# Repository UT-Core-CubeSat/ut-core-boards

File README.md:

# UT-CORE-BOARDS

PCB designs and board requirements for UT-CORE.

## Structure

Each subsystem contains its boards. Each board has the same three folders:

```text
<subsystem>/<board>/
├── hardware/       # Existing KiCad projects and their supporting files
├── docs/           # Board requirements and existing documentation
└── datasheets/     # Component datasheets and manufacturer references
```

Keep KiCad projects, libraries, models, schematic sheets, and other project
dependencies together. Existing revision folders, backups, manufacturing
outputs, and simulations are preserved inside `hardware/`.

## Boards

| Subsystem | Board requirements | Hardware |
|-----------|--------------------|----------|
| ADCS | [Controller](ADCS/controller/docs/adcs-board-requirements.md) | [Projects](ADCS/controller/hardware/) |
| ADCS | [Motor](ADCS/motor/docs/motor-board-requirements.md) | [Projects](ADCS/motor/hardware/) |
| CDH | [Controller](CDH/controller/docs/cdh-board-requirements.md) | [Projects](CDH/controller/hardware/) |
| EPS | [Battery](EPS/battery/docs/battery-board-requirements.md) | [Projects](EPS/battery/hardware/) |
| EPS | [Solar panel](EPS/solar-panel/docs/solar-panel-board-requirements.md) | [Projects](EPS/solar-panel/hardware/) |
| EPS | [Solar conglomerator](EPS/solar-conglomerator/docs/solar-conglomerator-board-requirements.md) | [Projects](EPS/solar-conglomerator/hardware/) |
| EPS | [Magtest](EPS/magtest/docs/magtest-board-requirements.md) | [PCB](EPS/magtest/hardware/) |
| GNSS | [Receiver](GNSS/receiver/docs/gnss-board-requirements.md) | [Projects](GNSS/receiver/hardware/) |

Solar panel variants stay together under `EPS/solar-panel/hardware/`, with
their original project folders intact. Both battery project bundles are
preserved under `EPS/battery/hardware/`. The standalone `magtest.kicad_pcb`
is preserved separately; its purpose and status still are undocumented.

## Board documents

Use [the template](templates/name-board-requirements.md) and name each document
`<name>-board-requirements.md`, using lowercase words separated by hyphens.
Existing documents and sheets remain alongside them in `docs/` as references.

The five sections cover purpose and design, specifications, interfaces,
operation and limitations, and notes. Keep detailed implementation and design
history in the board files and PRs. Identify the applicable PCB revision and
mark unknown or unverified information clearly.

Existing project-local libraries and models have not been consolidated or
renamed. Any datasheets already embedded in a project should stay there if
moving them could affect references; the new `datasheets/` folders are for
standalone references.

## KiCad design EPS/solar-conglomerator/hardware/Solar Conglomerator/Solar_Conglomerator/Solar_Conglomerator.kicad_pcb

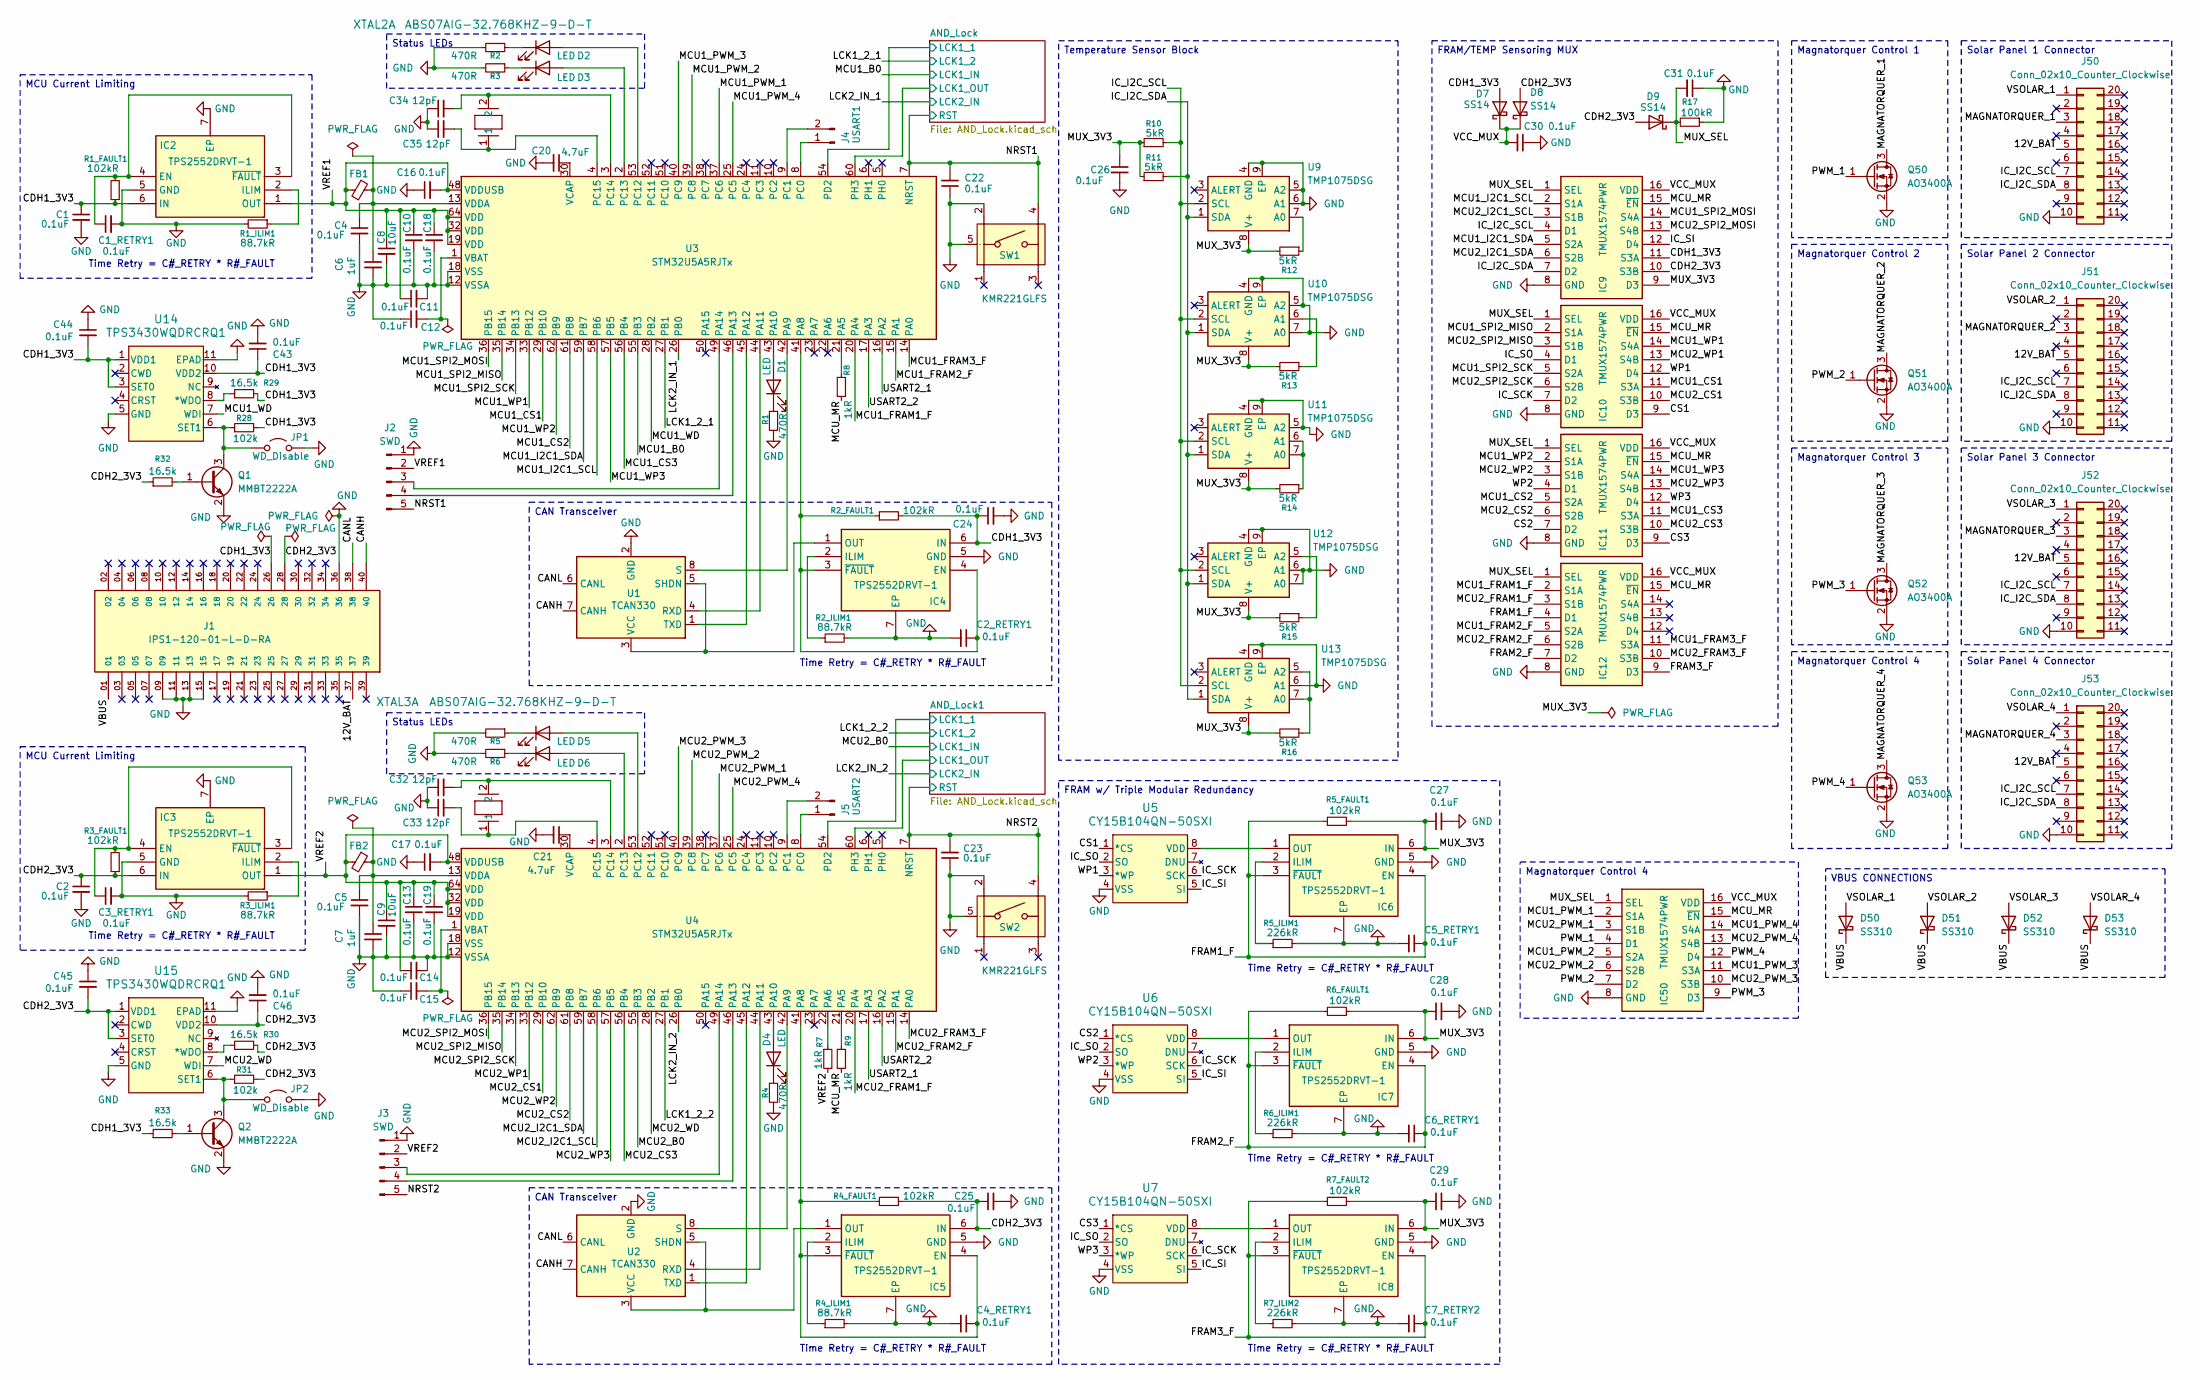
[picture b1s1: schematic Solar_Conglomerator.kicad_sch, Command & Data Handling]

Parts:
C1, C1_RETRY1, C2, C2_RETRY1, C3_RETRY1, C4, C4_RETRY1, C5, C5_RETRY1, C6_RETRY1, C7_RETRY2, C10, C11, C12, C13, C14, C15, C16, C17, C18, C19, C22, C23, C24, C25, C26, C27, C28, C29, C30, C31, C43, C44, C45, C46: 0.1uF; C_0603_1608Metric_Pad1.08x0.95mm_HandSolder
C6, C7: 1uF; C_0805_2012Metric_Pad1.18x1.45mm_HandSolder
C8, C9: 10uF; C_0805_2012Metric_Pad1.18x1.45mm_HandSolder
C20, C21: 4.7uF; C_0805_2012Metric_Pad1.18x1.45mm_HandSolder
C32, C33, C34, C35: 12pF; C_0603_1608Metric_Pad1.08x0.95mm_HandSolder
D1, D2, D3, D4, D5, D6: LED; LED_0201_0603Metric_Pad0.64x0.40mm_HandSolder
D7, D8, D9: SS14; D_SMA
D50, D51, D52, D53: SS310; D_SMA
FB1, FB2: FerriteBead_Small; R_0805_2012Metric_Pad1.20x1.40mm_HandSolder
IC2, IC3, IC4, IC5, IC6, IC7, IC8: TPS2552DRVT-1; Mouser Part Number 595-TPS2552DRVT-1
IC9, IC10, IC11, IC12, IC50: TMUX1574PWR; Mouser Part Number 595-TMUX1574PWR
J1: IPS1-120-01-L-D-RA
J2, J3: SWD; PinHeader_1x05_P2.54mm_Vertical
J4: USART1; PinHeader_1x02_P2.54mm_Vertical
J5: USART2; PinHeader_1x02_P2.54mm_Vertical
J50, J51, J52, J53: Conn_02x10_Counter_Clockwise; PinHeader_2x10_P2.54mm_Vertical
JP1, JP2: WD_Disable; TestPoint_2Pads_Pitch2.54mm_Drill0.8mm
Q1, Q2: MMBT2222A; SOT-23
Q50, Q51, Q52, Q53: AO3400A; SOT-23
R1, R2, R3, R4, R5, R6: 470R; R_0805_2012Metric_Pad1.20x1.40mm_HandSolder
R1_FAULT1, R2_FAULT1, R3_FAULT1, R4_FAULT1, R5_FAULT1, R6_FAULT1, R7_FAULT2: 102kR; R_0805_2012Metric_Pad1.20x1.40mm_HandSolder
R1_ILIM1, R2_ILIM1, R3_ILIM1, R4_ILIM1: 88.7kR; R_0805_2012Metric_Pad1.20x1.40mm_HandSolder
R5_ILIM1, R6_ILIM1, R7_ILIM2: 226kR; R_0805_2012Metric_Pad1.20x1.40mm_HandSolder
R7, R8, R9: 1kR; R_0805_2012Metric_Pad1.20x1.40mm_HandSolder
R10, R11, R12, R13, R14, R15, R16: 5kR; R_0603_1608Metric_Pad0.98x0.95mm_HandSolder
R17: 100kR; R_0805_2012Metric_Pad1.20x1.40mm_HandSolder
R28, R31: 102k; R_0805_2012Metric_Pad1.20x1.40mm_HandSolder
R29, R30, R32, R33: 16.5k; R_0805_2012Metric_Pad1.20x1.40mm_HandSolder
SW1, SW2: KMR221GLFS; Manufacturer Part KMR221GLFS; LCSC Part Name 4.6*2.8*1.9mm 立贴 轻触开关
U1, U2: TCAN330; SOIC-8_3.9x4.9mm_P1.27mm
U3, U4: STM32U5A5RJTx; LQFP-64_10x10mm_P0.5mm
U5, U6, U7: CY15B104QN-50SXI
U9, U10, U11, U12, U13: TMP1075DSG; WSON-8-1EP_2x2mm_P0.5mm_EP0.9x1.6mm
U14, U15: TPS3430WQDRCRQ1
XTAL2, XTAL3: ABS07AIG-32.768KHZ-9-D-T; XTAL_ABS07AIG_ABR

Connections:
/12V_BAT: J1.37, J50.5, J51.5, J52.5, J53.5
/AND_Lock1/LCK1_1: U4.54 (PD2); also elsewhere on the board
/AND_Lock1/LCK1_OUT: U4.60 (PH3); also elsewhere on the board
/AND_Lock/LCK1_1: U3.54 (PD2); also elsewhere on the board
/AND_Lock/LCK1_OUT: U3.60 (PH3); also elsewhere on the board
/CANH: J1.40, U1.7 (CANH), U2.7 (CANH)
/CANL: J1.38, U1.6 (CANL), U2.6 (CANL)
/CDH1_3V3: C1.1, C24.1, C43.1, C44.2, D7.2 (A), IC2.6 (IN), IC4.6 (IN), IC9.11 (S3A), J1.26, R1_FAULT1.1, R2_FAULT1.2, R28.2, R29.2, R33.1, U14.1 (VDD1), U14.3 (SET0), U14.10 (VDD2); also elsewhere on the board
/CDH2_3V3: C2.1, C25.1, C45.2, C46.1, D8.2 (A), D9.2 (A), IC3.6 (IN), IC5.6 (IN), IC9.10 (S3B), J1.28, R3_FAULT1.1, R4_FAULT1.2, R30.2, R31.2, R32.1, U15.1 (VDD1), U15.3 (SET0), U15.10 (VDD2); also elsewhere on the board
/CS1: IC10.9 (D3), U5.1 (*CS)
/CS2: IC11.7 (D2), U6.1 (*CS)
/CS3: IC11.9 (D3), U7.1 (*CS)
/FRAM1_F: C5_RETRY1.1, IC6.3 (~FAULT), IC6.4 (EN), IC12.4 (D1), R5_FAULT1.1
/FRAM2_F: C6_RETRY1.1, IC7.3 (~FAULT), IC7.4 (EN), IC12.7 (D2), R6_FAULT1.1
/FRAM3_F: C7_RETRY2.1, IC8.3 (~FAULT), IC8.4 (EN), IC12.9 (D3), R7_FAULT2.1
/IC_I2C_SCL: IC9.4 (D1), J50.7, J51.7, J52.7, J53.7, R10.2, U9.2 (SCL), U10.2 (SCL), U11.2 (SCL), U12.2 (SCL), U13.2 (SCL)
/IC_I2C_SDA: IC9.7 (D2), J50.8, J51.8, J52.8, J53.8, R11.2, U9.1 (SDA), U10.1 (SDA), U11.1 (SDA), U12.1 (SDA), U13.1 (SDA)
/IC_SCK: IC10.7 (D2), U5.6 (SCK), U6.6 (SCK), U7.6 (SCK)
/IC_SI: IC9.12 (D4), U5.5 (SI), U6.5 (SI), U7.5 (SI)
/IC_SO: IC10.4 (D1), U5.2 (SO), U6.2 (SO), U7.2 (SO)
/LCK1_2_1: U3.27 (PB1); also elsewhere on the board
/LCK1_2_2: U4.27 (PB1); also elsewhere on the board
/LCK2_IN_1: U3.26 (PB0); also elsewhere on the board
/LCK2_IN_2: U4.26 (PB0); also elsewhere on the board
/MAGNATORQUER_1: J50.3, Q50.3 (D)
/MAGNATORQUER_2: J51.3, Q51.3 (D)
/MAGNATORQUER_3: J52.3, Q52.3 (D)
/MAGNATORQUER_4: J53.3, Q53.3 (D)
/MCU1_B0: U3.55 (PB3); also elsewhere on the board
/MCU1_CS1: IC10.11 (S3A), U3.29 (PB10)
/MCU1_CS2: IC11.5 (S2A), U3.61 (PB8)
/MCU1_CS3: IC11.11 (S3A), U3.56 (PB4)
/MCU1_FRAM1_F: IC12.2 (S1A), U3.20 (PA4)
/MCU1_FRAM2_F: IC12.5 (S2A), U3.15 (PA1)
/MCU1_FRAM3_F: IC12.11 (S3A), U3.14 (PA0)
/MCU1_I2C1_SCL: IC9.2 (S1A), U3.58 (PB6)
/MCU1_I2C1_SDA: IC9.5 (S2A), U3.59 (PB7)
/MCU1_PWM_1: IC50.2 (S1A), U3.37 (PC6)
/MCU1_PWM_2: IC50.5 (S2A), U3.39 (PC8)
/MCU1_PWM_3: IC50.11 (S3A), U3.40 (PC9)
/MCU1_PWM_4: IC50.14 (S4A), U3.25 (PC5)
/MCU1_SPI2_MISO: IC10.2 (S1A), U3.35 (PB14)
/MCU1_SPI2_MOSI: IC9.14 (S4A), U3.36 (PB15)
/MCU1_SPI2_SCK: IC10.5 (S2A), U3.34 (PB13)
/MCU1_WD: U3.28 (PB2), U14.7 (WDI)
/MCU1_WP1: IC10.14 (S4A), U3.33 (PB12)
/MCU1_WP2: IC11.2 (S1A), U3.62 (PB9)
/MCU1_WP3: IC11.14 (S4A), U3.57 (PB5)
/MCU2_B0: U4.55 (PB3); also elsewhere on the board
/MCU2_CS1: IC10.10 (S3B), U4.29 (PB10)
/MCU2_CS2: IC11.6 (S2B), U4.61 (PB8)
/MCU2_CS3: IC11.10 (S3B), U4.56 (PB4)
/MCU2_FRAM1_F: IC12.3 (S1B), U4.20 (PA4)
/MCU2_FRAM2_F: IC12.6 (S2B), U4.15 (PA1)
/MCU2_FRAM3_F: IC12.10 (S3B), U4.14 (PA0)
/MCU2_I2C1_SCL: IC9.3 (S1B), U4.58 (PB6)
/MCU2_I2C1_SDA: IC9.6 (S2B), U4.59 (PB7)
/MCU2_PWM_1: IC50.3 (S1B), U4.37 (PC6)
/MCU2_PWM_2: IC50.6 (S2B), U4.39 (PC8)
/MCU2_PWM_3: IC50.10 (S3B), U4.40 (PC9)
/MCU2_PWM_4: IC50.13 (S4B), U4.25 (PC5)
/MCU2_SPI2_MISO: IC10.3 (S1B), U4.35 (PB14)
/MCU2_SPI2_MOSI: IC9.13 (S4B), U4.36 (PB15)
/MCU2_SPI2_SCK: IC10.6 (S2B), U4.34 (PB13)
/MCU2_WD: U4.28 (PB2), U15.7 (WDI)
/MCU2_WP1: IC10.13 (S4B), U4.33 (PB12)
/MCU2_WP2: IC11.3 (S1B), U4.62 (PB9)
/MCU2_WP3: IC11.13 (S4B), U4.57 (PB5)
/MCU_MR: IC9.15 (~EN), IC10.15 (~EN), IC11.15 (~EN), IC12.15 (~EN), IC50.15 (~EN), R8.2, R9.2
/MUX_3V3: C26.1, C27.1, C28.1, C29.1, IC6.6 (IN), IC7.6 (IN), IC8.6 (IN), IC9.9 (D3), R5_FAULT1.2, R6_FAULT1.2, R7_FAULT2.2, R10.1, R11.1, R12.2, R13.2, R14.2, R15.2, R16.2, U9.8 (V+), U10.8 (V+), U11.8 (V+), U12.8 (V+), U13.8 (V+)
/MUX_SEL: C31.2, D9.1 (K), IC9.1 (SEL), IC10.1 (SEL), IC11.1 (SEL), IC12.1 (SEL), IC50.1 (SEL), R17.2
/NRST1: C22.2, J2.5, SW1.4, U3.7 (NRST); also elsewhere on the board
/NRST2: C23.2, J3.5, SW2.4, U4.7 (NRST); also elsewhere on the board
/PWM_1: IC50.4 (D1), Q50.1 (G)
/PWM_2: IC50.7 (D2), Q51.1 (G)
/PWM_3: IC50.9 (D3), Q52.1 (G)
/PWM_4: IC50.12 (D4), Q53.1 (G)
/USART2_1: U3.16 (PA2), U4.17 (PA3)
/USART2_2: U3.17 (PA3), U4.16 (PA2)
/VBUS: D50.1 (K), D51.1 (K), D52.1 (K), D53.1 (K), J1.01
/VCC_MUX: C30.2, D7.1 (K), D8.1 (K), IC9.16 (VDD), IC10.16 (VDD), IC11.16 (VDD), IC12.16 (VDD), IC50.16 (VDD)
/VREF1: C8.1, C10.1, C11.1, C16.2, C18.1, FB1.2, IC2.1 (OUT), J2.2, U3.19 (VDD), U3.32 (VDD), U3.48 (VDDUSB), U3.64 (VDD)
/VREF2: C9.1, C13.1, C14.1, C17.2, C19.1, FB2.2, IC3.1 (OUT), J3.2, R7.2, U4.19 (VDD), U4.32 (VDD), U4.48 (VDDUSB), U4.64 (VDD)
/VSOLAR_1: D50.2 (A), J50.1
/VSOLAR_2: D51.2 (A), J51.1
/VSOLAR_3: D52.2 (A), J52.1
/VSOLAR_4: D53.2 (A), J53.1
/WP1: IC10.12 (D4), U5.3 (*WP)
/WP2: IC11.4 (D1), U6.3 (*WP)
/WP3: IC11.12 (D4), U7.3 (*WP)
GND: C1.2, C1_RETRY1.2, C2.2, C2_RETRY1.2, C3_RETRY1.2, C4.2, C4_RETRY1.2, C5.2, C5_RETRY1.2, C6.2, C6_RETRY1.2, C7.2, C7_RETRY2.2, C8.2, C9.2, C10.2, C11.2, C12.1, C13.2, C14.2, C15.1, C16.1, C17.1, C18.2, C19.2, C20.2, C21.2, C22.1, C23.1, C24.2, C25.2, C26.2, C27.2, C28.2, C29.2, C30.1, C31.1, C32.1, C33.1, C34.1, C35.1, C43.2, C44.1, C45.1, C46.2, IC2.5 (GND), IC2.7 (EP), IC3.5 (GND), IC3.7 (EP), IC4.5 (GND), IC4.7 (EP), IC5.5 (GND), IC5.7 (EP), IC6.5 (GND), IC6.7 (EP), IC7.5 (GND), IC7.7 (EP), IC8.5 (GND), IC8.7 (EP), IC9.8 (GND), IC10.8 (GND), IC11.8 (GND), IC12.8 (GND), IC50.8 (GND), J1.09, J1.11, J1.13, J1.15, J1.36, J2.1, J3.1, J50.10, J51.10, J52.10, J53.10, JP1.2 (B), JP2.2 (B), Q1.2 (E), Q2.2 (E), Q50.2 (S), Q51.2 (S), Q52.2 (S), Q53.2 (S), R1.2, R1_ILIM1.2, R2.2, R2_ILIM1.2, R3.2, R3_ILIM1.2, R4.2, R4_ILIM1.2, R5.2, R5_ILIM1.2, R6.2, R6_ILIM1.2, R7_ILIM2.2, R17.1, SW1.2, SW1.5, SW2.2, SW2.5, U1.2 (GND), U2.2 (GND), U3.12 (VSSA), U3.18 (VSS), U3.31 (VSS), U3.47 (VSS), U3.63 (VSS), U4.12 (VSSA), U4.18 (VSS), U4.31 (VSS), U4.47 (VSS), U4.63 (VSS), U5.4 (VSS), U6.4 (VSS), U7.4 (VSS), U9.4 (GND), U9.5 (A2), U9.6 (A1), U9.9 (EP), U10.4 (GND), U10.5 (A2), U10.7 (A0), U10.9 (EP), U11.4 (GND), U11.5 (A2), U11.9 (EP), U12.4 (GND), U12.6 (A1), U12.7 (A0), U12.9 (EP), U13.4 (GND), U13.6 (A1), U13.9 (EP), U14.5 (GND), U14.11 (EPAD), U15.5 (GND), U15.11 (EPAD); also elsewhere on the board
unnamed: D1.2 (A), U3.43 (PA10)
unnamed: D1.1 (K), R1.1
unnamed: D2.2 (A), U3.53 (PC12)
unnamed: D2.1 (K), R2.1
unnamed: D3.2 (A), U3.2 (PC13)
unnamed: D3.1 (K), R3.1
unnamed: D4.2 (A), U4.43 (PA10)
unnamed: D4.1 (K), R4.1
unnamed: D5.2 (A), U4.53 (PC12)
unnamed: D5.1 (K), R5.1
unnamed: D6.2 (A), U4.2 (PC13)
unnamed: D6.1 (K), R6.1
unnamed: C1_RETRY1.1, IC2.3 (~FAULT), IC2.4 (EN), R1_FAULT1.2
unnamed: IC2.2 (ILIM), R1_ILIM1.1
unnamed: C3_RETRY1.1, IC3.3 (~FAULT), IC3.4 (EN), R3_FAULT1.2
unnamed: IC3.2 (ILIM), R3_ILIM1.1
unnamed: C2_RETRY1.1, IC4.3 (~FAULT), IC4.4 (EN), R2_FAULT1.1, U3.41 (PA8)
unnamed: IC4.2 (ILIM), R2_ILIM1.1
unnamed: IC4.1 (OUT), U1.3 (VCC), U1.5 (SHDN)
unnamed: C4_RETRY1.1, IC5.3 (~FAULT), IC5.4 (EN), R4_FAULT1.1, U4.41 (PA8)
unnamed: IC5.2 (ILIM), R4_ILIM1.1
unnamed: IC5.1 (OUT), U2.3 (VCC), U2.5 (SHDN)
unnamed: IC6.2 (ILIM), R5_ILIM1.1
unnamed: IC6.1 (OUT), U5.8 (VDD)
unnamed: IC7.2 (ILIM), R6_ILIM1.1
unnamed: IC7.1 (OUT), U6.8 (VDD)
unnamed: IC8.2 (ILIM), R7_ILIM2.1
unnamed: IC8.1 (OUT), U7.8 (VDD)
unnamed: J2.3, U3.49 (PA14)
unnamed: J2.4, U3.46 (PA13)
unnamed: J3.3, U4.49 (PA14)
unnamed: J3.4, U4.46 (PA13)
unnamed: J4.1, U3.8 (PC0)
unnamed: J4.2, U3.9 (PC1)
unnamed: J5.1, U4.8 (PC0)
unnamed: J5.2, U4.9 (PC1)
unnamed: JP1.1 (A), Q1.3 (C), R28.1, U14.6 (SET1)
unnamed: JP2.1 (A), Q2.3 (C), R31.1, U15.6 (SET1)
unnamed: Q1.1 (B), R32.2
unnamed: Q2.1 (B), R33.2
unnamed: U1.4 (RXD), U3.44 (PA11)
unnamed: U1.8 (S), U3.42 (PA9)
unnamed: U1.1 (TXD), U3.45 (PA12)
unnamed: U2.4 (RXD), U4.44 (PA11)
unnamed: U2.8 (S), U4.42 (PA9)
unnamed: U2.1 (TXD), U4.45 (PA12)
unnamed: R8.1, U3.21 (PA5)
unnamed: C34.2, U3.3 (PC14), XTAL2.2
unnamed: C35.2, U3.4 (PC15), XTAL2.1
unnamed: C12.2, U3.1 (VBAT)
unnamed: C20.1, U3.30 (VCAP)
unnamed: C4.1, C6.1, FB1.1, U3.13 (VDDA)
unnamed: R9.1, U4.21 (PA5)
unnamed: R7.1, U4.22 (PA6)
unnamed: C32.2, U4.3 (PC14), XTAL3.2
unnamed: C33.2, U4.4 (PC15), XTAL3.1
unnamed: C15.2, U4.1 (VBAT)
unnamed: C21.1, U4.30 (VCAP)
unnamed: C5.1, C7.1, FB2.1, U4.13 (VDDA)
unnamed: R12.1, U9.7 (A0)
unnamed: R13.1, U10.6 (A1)
unnamed: R14.1, U11.6 (A1), U11.7 (A0)
unnamed: R15.1, U12.5 (A2)
unnamed: R16.1, U13.5 (A2), U13.7 (A0)
unnamed: R29.1, U14.8 (*WDO)
unnamed: R30.1, U15.8 (*WDO)

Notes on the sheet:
Time Retry = C#_RETRY * R#_FAULT
Magnatorquer Control 2
Magnatorquer Control 4
Solar Panel 1 Connector
Status LEDs
Magnatorquer Control 1
CAN Transceiver
Magnatorquer Control 3
Temperature Sensor Block
FRAM w/ Triple Modular Redundancy
FRAM/TEMP Sensoring MUX
Solar Panel 4 Connector
VBUS CONNECTIONS
Solar Panel 2 Connector
Solar Panel 3 Connector
MCU Current Limiting

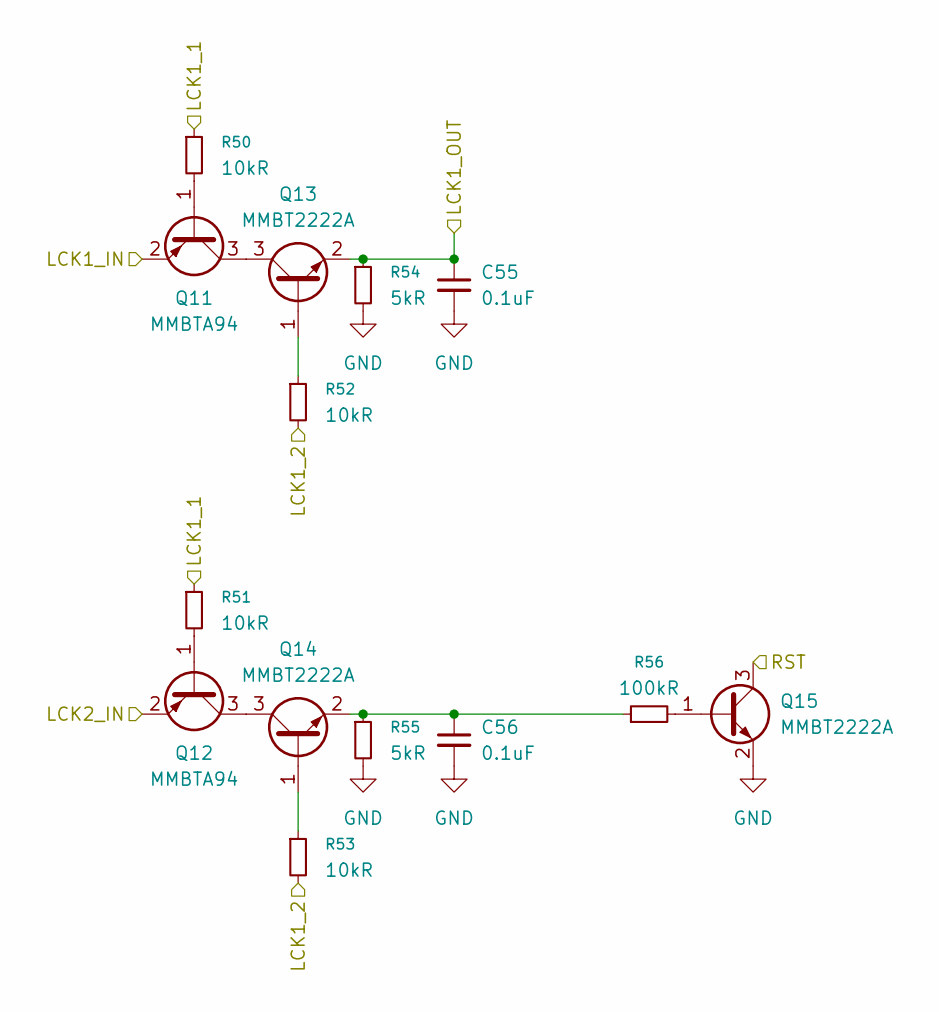
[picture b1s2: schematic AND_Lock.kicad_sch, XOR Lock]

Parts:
C55, C56: 0.1uF; C_0603_1608Metric_Pad1.08x0.95mm_HandSolder
Q11, Q12: MMBTA94; SOT-23
Q13, Q14, Q15: MMBT2222A; SOT-23
R50, R51, R52, R53: 10kR; R_0805_2012Metric_Pad1.20x1.40mm_HandSolder
R54, R55: 5kR; R_0805_2012Metric_Pad1.20x1.40mm_HandSolder
R56: 100kR; R_0805_2012Metric_Pad1.20x1.40mm_HandSolder

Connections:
/AND_Lock/LCK1_1: R50.1, R51.1; also elsewhere on the board
/AND_Lock/LCK1_OUT: C55.1, Q13.2 (E), R54.1; also elsewhere on the board
/LCK1_2_1: R52.2, R53.2; also elsewhere on the board
/LCK2_IN_1: Q12.2 (E); also elsewhere on the board
/MCU1_B0: Q11.2 (E); also elsewhere on the board
/NRST1: Q15.3 (C); also elsewhere on the board
GND: C55.2, C56.2, Q15.2 (E), R54.2, R55.2; also elsewhere on the board
unnamed: Q11.1 (B), R50.2
unnamed: Q11.3 (C), Q13.3 (C)
unnamed: Q12.1 (B), R51.2
unnamed: Q12.3 (C), Q14.3 (C)
unnamed: Q13.1 (B), R52.1
unnamed: Q14.1 (B), R53.1
unnamed: C56.1, Q14.2 (E), R55.1, R56.1
unnamed: Q15.1 (B), R56.2

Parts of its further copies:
C57, C58: 0.1uF; C_0603_1608Metric_Pad1.08x0.95mm_HandSolder
Q16, Q17: MMBTA94; SOT-23
Q18, Q19, Q20: MMBT2222A; SOT-23
R57, R58, R59, R60: 10kR; R_0805_2012Metric_Pad1.20x1.40mm_HandSolder
R61, R62: 5kR; R_0805_2012Metric_Pad1.20x1.40mm_HandSolder
R63: 100kR; R_0805_2012Metric_Pad1.20x1.40mm_HandSolder

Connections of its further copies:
/AND_Lock1/LCK1_1: R57.1, R58.1; also elsewhere on the board
/AND_Lock1/LCK1_OUT: C57.1, Q18.2 (E), R61.1; also elsewhere on the board
/LCK1_2_2: R59.2, R60.2; also elsewhere on the board
/LCK2_IN_2: Q17.2 (E); also elsewhere on the board
/MCU2_B0: Q16.2 (E); also elsewhere on the board
/NRST2: Q20.3 (C); also elsewhere on the board
GND: C57.2, C58.2, Q20.2 (E), R61.2, R62.2; also elsewhere on the board
unnamed: Q16.1 (B), R57.2
unnamed: Q16.3 (C), Q18.3 (C)
unnamed: Q17.1 (B), R58.2
unnamed: Q17.3 (C), Q19.3 (C)
unnamed: Q18.1 (B), R59.1
unnamed: Q19.1 (B), R60.1
unnamed: C58.1, Q19.2 (E), R62.1, R63.1
unnamed: Q20.1 (B), R63.2

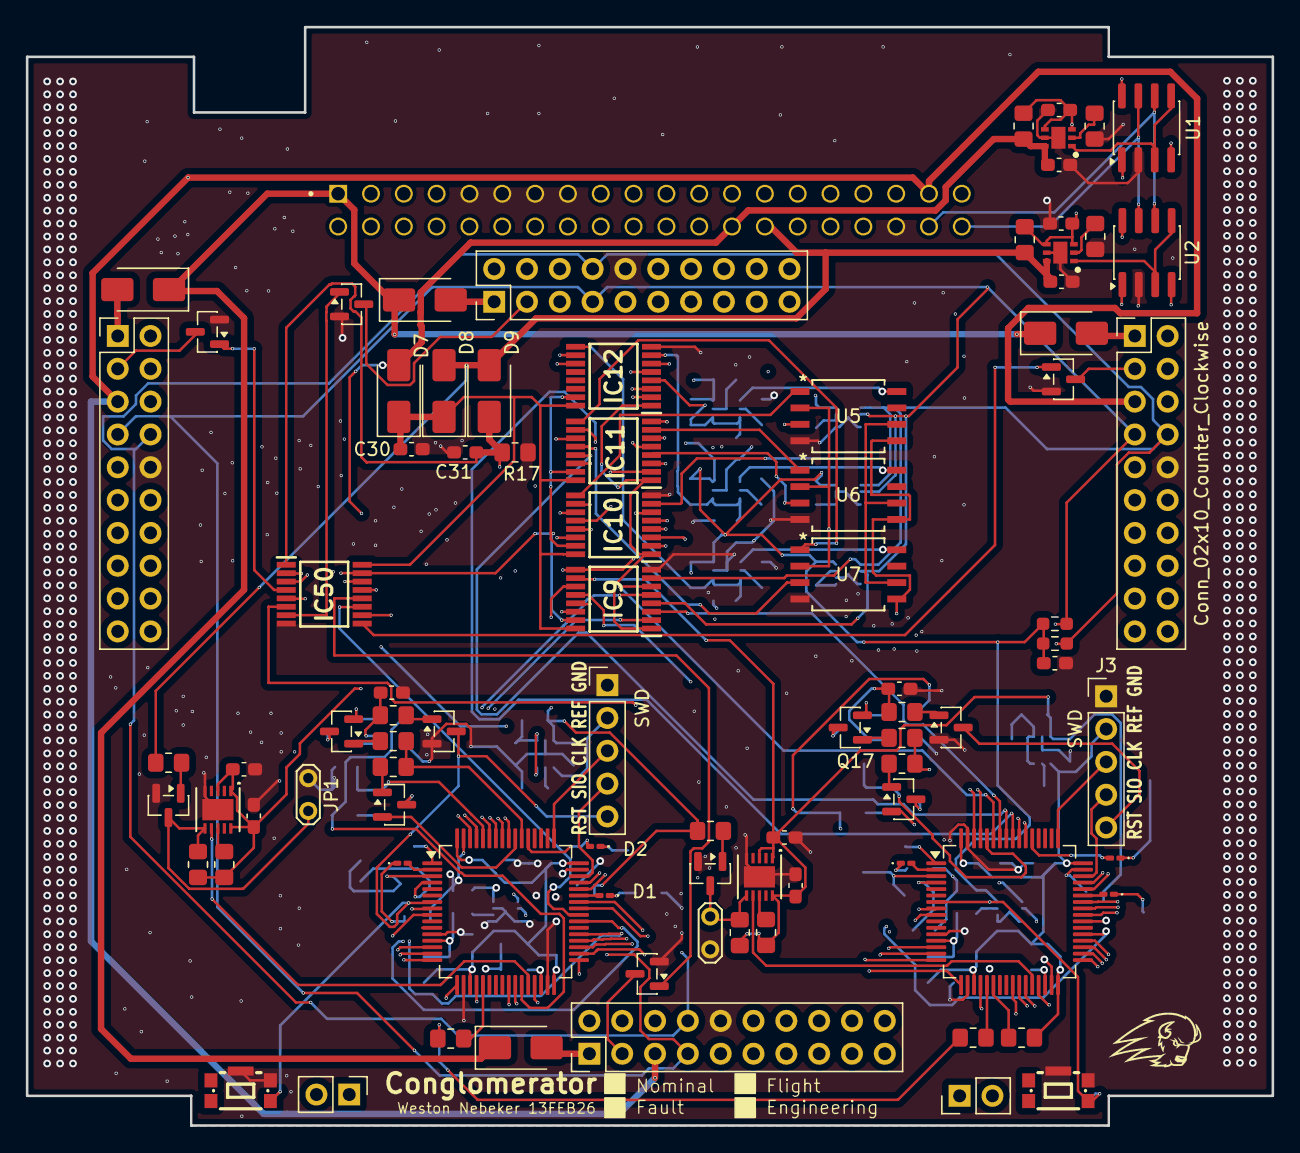
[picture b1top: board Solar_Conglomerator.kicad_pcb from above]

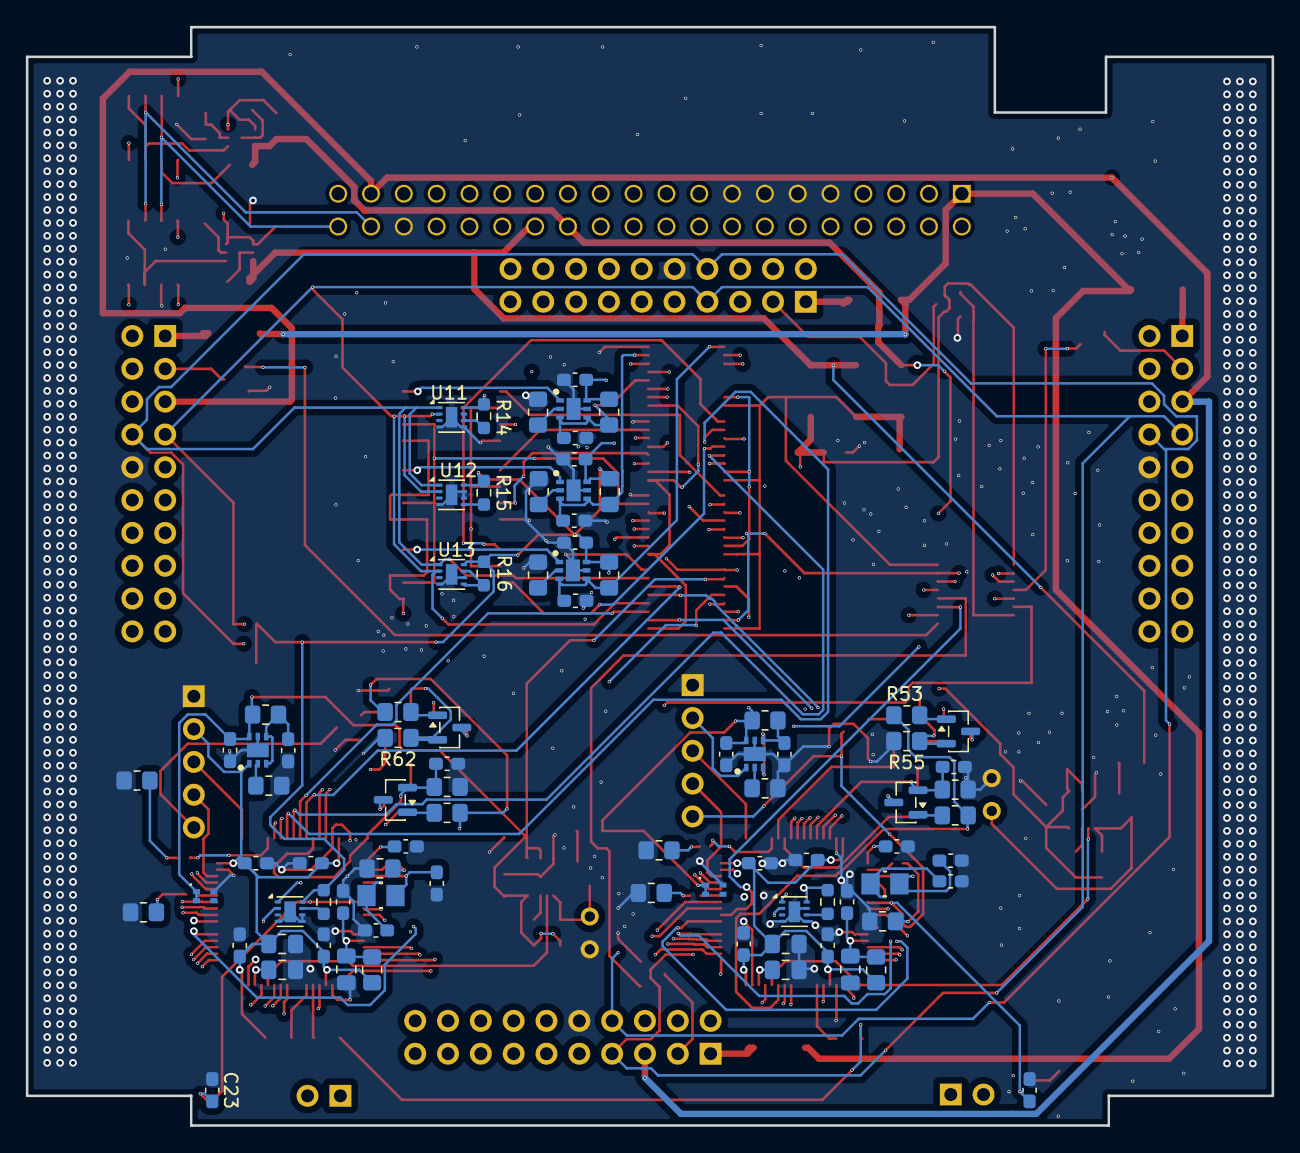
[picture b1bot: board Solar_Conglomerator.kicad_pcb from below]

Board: 4 copper layers, 96.4 x 85.0 mm, 174 parts (85 on the bottom side), 173 nets.

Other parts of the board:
U17, U18: ATXK-H14

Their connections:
/CDH1_3V3: U17.1 (EN), U17.4 (VDD); also elsewhere on the board
/CDH2_3V3: U18.1 (EN), U18.4 (VDD); also elsewhere on the board
GND: U17.2 (GND), U18.2 (GND); also elsewhere on the board

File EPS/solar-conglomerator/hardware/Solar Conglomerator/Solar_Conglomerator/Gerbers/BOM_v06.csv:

0.1uF,"C1,C1_RETRY1,C2,C2_RETRY1,C3,C3_RETRY1,C4,C4_RETRY1,C5,C5_RETRY1,C6_RETRY1,C7_RETRY1,C7_RETRY2,C10,C11,C12,C13,C14,C15,C16,C17,C18,C19,C22,C23,C24,C25,C26,C27,C28,C29,C30,C31,C43,C44,C45,C46,C47,C55,C56,C57,C58",603,C1864275
1uF,"C6,C7",805,C1865372
10uF,"C8,C9",805,C696369
4.7uF,"C20,C21,C37,C48",805,C1883316
12pF,"C32,C33,C34,C35",603,
0.1uF,"C36,C38",805,C1864275
LED,"D1,D4",201,C5440628
LED,"D2,D5",201,C3646921
LED,"D3,D6",201,C3646923
SS14,"D7,D8,D9",DO-214AC,C47460
FerriteBead_Small,"FB1,FB2",805,C85840
TPS2552DRVT-1,"IC1,IC2,IC3,IC4,IC5,IC6,IC7,IC8",WSON-6,C2150036
TMUX1574PWR,"IC9,IC10,IC11,IC12,IC13,IC14,IC15",TSSOP-16,C2673443
MMBT2222A,"Q1,Q2,Q13,Q14,Q15,Q18,Q19,Q20",SOT-23,
MMBTA94,"Q11,Q12,Q16,Q17",SOT-23,
470R,"R1,R2,R3,R4,R5,R6",805,C186245
102kR,"R1_FAULT1,R2_FAULT1,R3_FAULT1,R4_FAULT1,R5_FAULT1,R6_FAULT1,R7_FAULT1,R7_FAULT2",805,C2510746
88.7kR,"R1_ILIM1,R2_ILIM1,R3_ILIM1,R4_ILIM1",805,C2511382
226kR,"R5_ILIM1,R6_ILIM1,R7_ILIM2",805,C2509529
1kR,"R7,R8,R9",805,C186253
108kR,R7_ILIM1,805,C2538862
5kR,"R10,R11,R12,R13,R14,R15,R16",805,C6407682
100kR,"R17,R56,R63",805,C186301
10kR,"R18,R19,R20,R22,R23,R24,R25,R26,R27,R50,R51,R52,R53,R57,R58,R59,R60",805,C186269
22.1kR,R21,805,C186277
102k,"R28,R31",805,C2539116
16.5k,"R29,R30,R32,R33",805,C4162440
5kR,"R54,R55,R61,R62",805,C2538569
KMR221GLFS,"SW1,SW2","SMD,4.6x2.8mm",C72443
TCAN330,"U1,U2",SOIC-8,C31086109
STM32U5A5RJTx,"U3,U4",LQFP-64(10x10),C22454506
CY15B104QN-50SXI,"U5,U6,U7",SOIC-8,C2954184
TMP1075DSG,"U8,U9,U10,U11,U12,U13",WSON-8,C2870250
TPS3430WQDRCRQ1,"U14,U15",VSON-10-EP(3x3),C2651379
SDINBDG4-8G,U16,BGA-153,C577444
ABS07AIG-32.768KHZ-9-D-T,"U17,U18",SMD3215-2P,C6491654

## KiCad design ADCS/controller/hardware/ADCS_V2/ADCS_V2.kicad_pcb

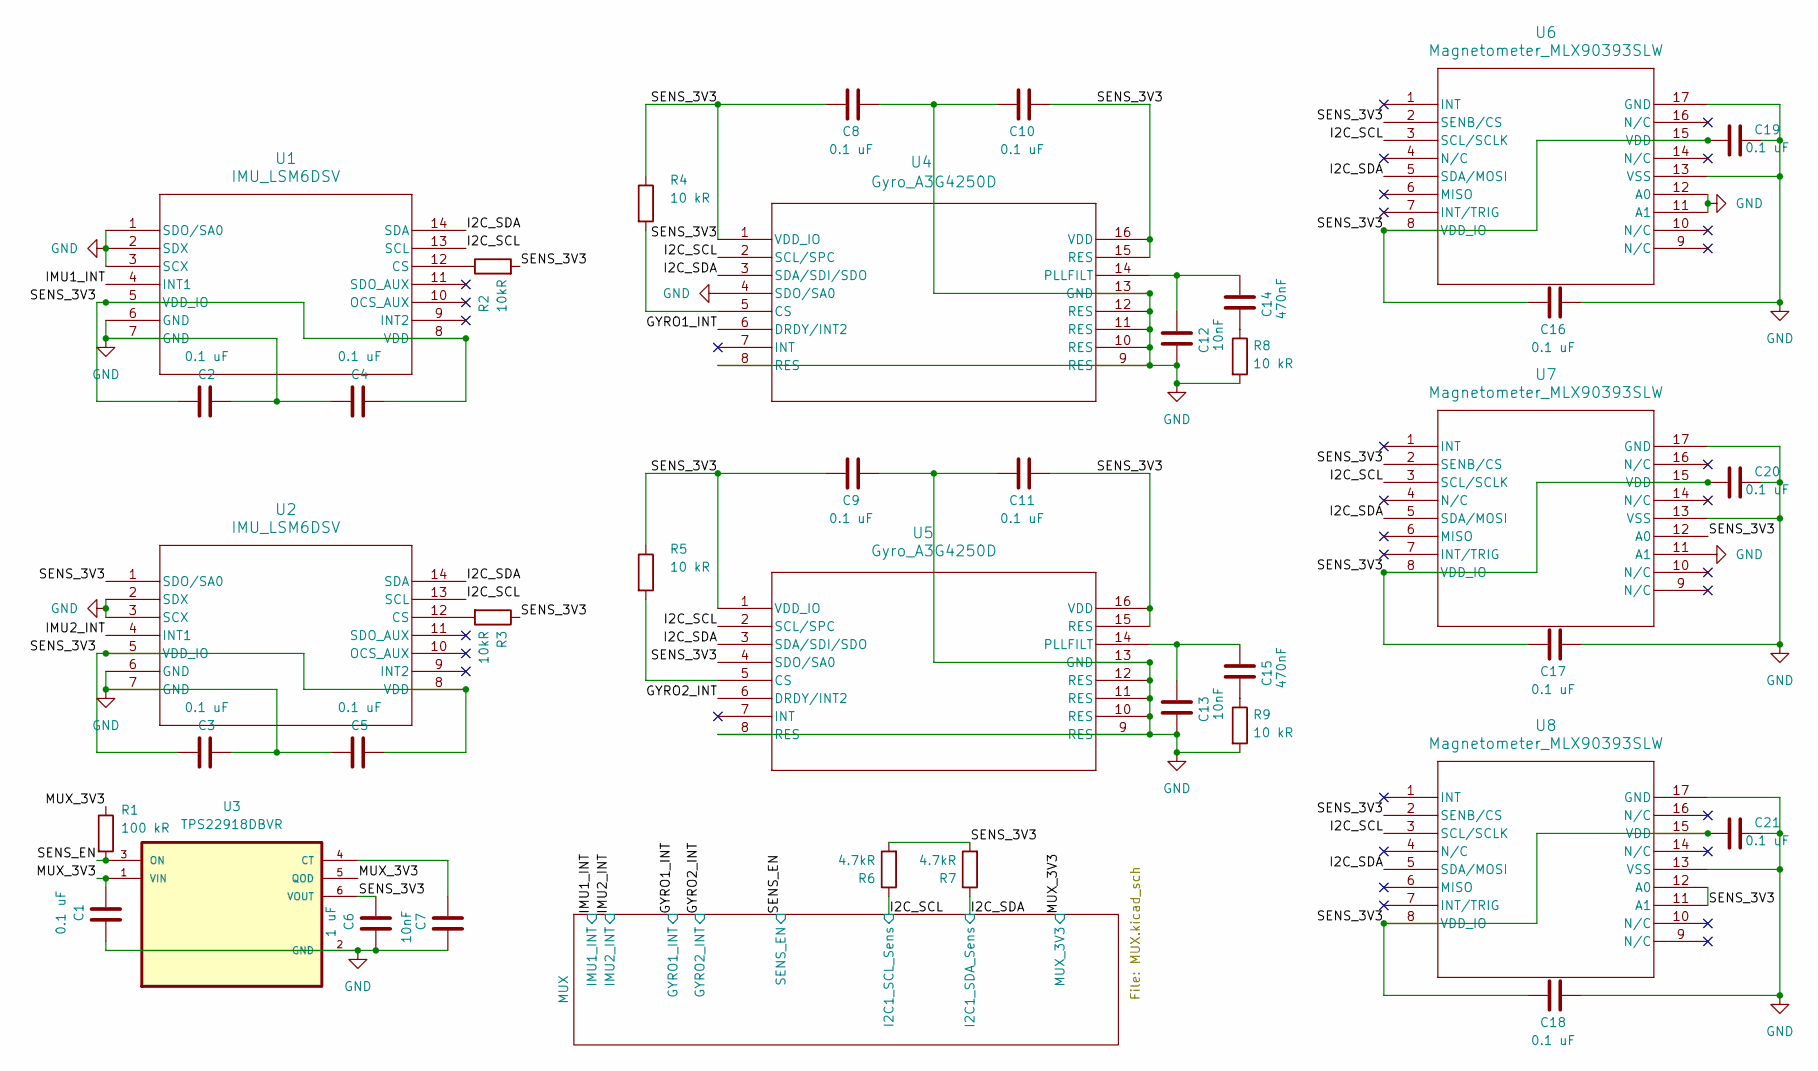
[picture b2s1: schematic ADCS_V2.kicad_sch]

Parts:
C1, C2, C3, C4, C5, C8, C9, C10, C11, C16, C17, C18, C19, C20, C21: 0.1 uF; C_0603_1608Metric
C6: 1 uF; C_0603_1608Metric
C7, C12, C13: 10nF; C_0603_1608Metric
C14, C15: 470nF; C_0603_1608Metric
R1: 100 kR; R_0603_1608Metric
R2, R3: 10kR; R_0603_1608Metric
R4, R5, R8, R9: 10 kR; R_0603_1608Metric
R6, R7: 4.7kR; R_0603_1608Metric
U1, U2: IMU_LSM6DSV; LGA14-L_2P59X3P1X0P5_STM
U3: TPS22918DBVR; SOT-23-6
U4, U5: Gyro_A3G4250D; LGA-16_4X4X1P1_STM
U6, U7, U8: Magnetometer_MLX90393SLW; QFN-16_MLX90393_MEL

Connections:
/GYRO1_INT: U4.6 (DRDY/INT2); also elsewhere on the board
/GYRO2_INT: U5.6 (DRDY/INT2); also elsewhere on the board
/I2C_SCL: R6.1, U1.13 (SCL), U2.13 (SCL), U4.2 (SCL/SPC), U5.2 (SCL/SPC), U6.3 (SCL/SCLK), U7.3 (SCL/SCLK), U8.3 (SCL/SCLK); also elsewhere on the board
/I2C_SDA: R7.1, U1.14 (SDA), U2.14 (SDA), U4.3 (SDA/SDI/SDO), U5.3 (SDA/SDI/SDO), U6.5 (SDA/MOSI), U7.5 (SDA/MOSI), U8.5 (SDA/MOSI); also elsewhere on the board
/IMU1_INT: U1.4 (INT1); also elsewhere on the board
/IMU2_INT: U2.4 (INT1); also elsewhere on the board
/MUX_3V3: C1.1, R1.1, U3.1 (VIN), U3.5 (QOD); also elsewhere on the board
/SENS_3V3: C2.2, C3.2, C4.1, C5.1, C6.1, C8.1, C9.1, C10.2, C11.2, C16.1, C17.1, C18.1, C19.1, C20.1, C21.1, R2.2, R3.1, R4.1, R5.1, R6.2, R7.2, U1.5 (VDD_IO), U1.8 (VDD), U2.1 (SDO/SA0), U2.5 (VDD_IO), U2.8 (VDD), U3.6 (VOUT), U4.1 (VDD_IO), U4.15 (RES), U4.16 (VDD), U5.1 (VDD_IO), U5.4 (SDO/SA0), U5.15 (RES), U5.16 (VDD), U6.2 (SENB/CS), U6.8 (VDD_IO), U6.15 (VDD), U7.2 (SENB/CS), U7.8 (VDD_IO), U7.12 (A0), U7.15 (VDD), U8.2 (SENB/CS), U8.8 (VDD_IO), U8.11 (A1), U8.12 (A0), U8.15 (VDD)
/SENS_EN: R1.2, U3.3 (ON); also elsewhere on the board
GND: C1.2, C2.1, C3.1, C4.2, C5.2, C6.2, C7.2, C8.2, C9.2, C10.1, C11.1, C12.1, C13.1, C16.2, C17.2, C18.2, C19.2, C20.2, C21.2, R8.2, R9.2, U1.1 (SDO/SA0), U1.2 (SDX), U1.3 (SCX), U1.6 (GND), U1.7 (GND), U2.2 (SDX), U2.3 (SCX), U2.6 (GND), U2.7 (GND), U3.2 (GND), U4.4 (SDO/SA0), U4.8 (RES), U4.9 (RES), U4.10 (RES), U4.11 (RES), U4.12 (RES), U4.13 (GND), U5.8 (RES), U5.9 (RES), U5.10 (RES), U5.11 (RES), U5.12 (RES), U5.13 (GND), U6.11 (A1), U6.12 (A0), U6.13 (VSS), U6.17 (GND), U7.11 (A1), U7.13 (VSS), U7.17 (GND), U8.13 (VSS), U8.17 (GND); also elsewhere on the board
unnamed: C14.1, R8.1
unnamed: C15.1, R9.1
unnamed: R2.1, U1.12 (CS)
unnamed: R3.2, U2.12 (CS)
unnamed: C7.1, U3.4 (CT)
unnamed: R4.2, U4.5 (CS)
unnamed: C12.2, C14.2, U4.14 (PLLFILT)
unnamed: R5.2, U5.5 (CS)
unnamed: C13.2, C15.2, U5.14 (PLLFILT)

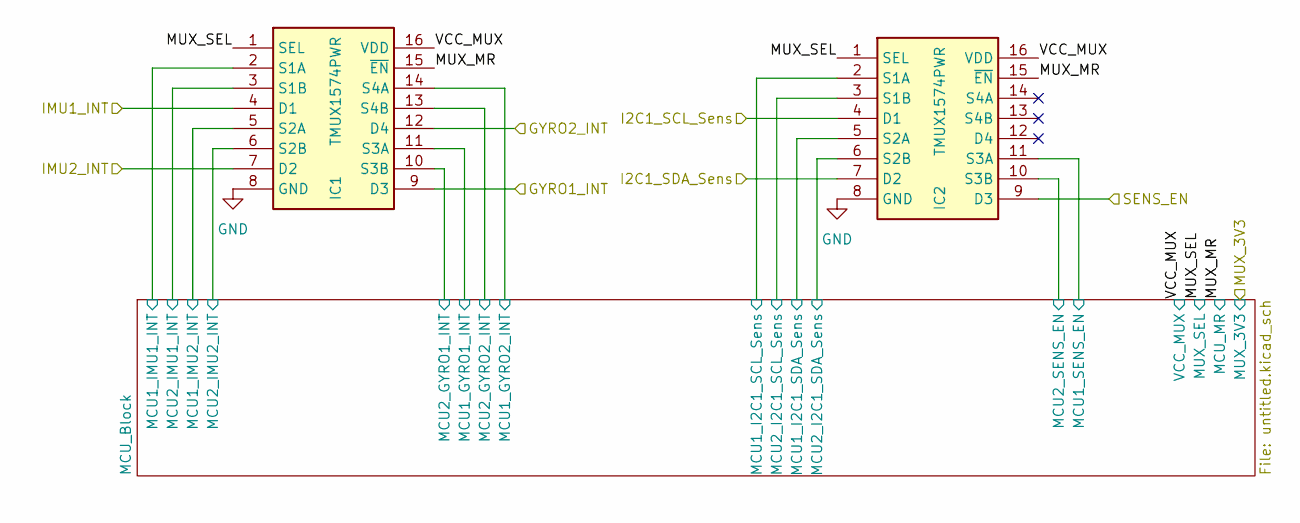
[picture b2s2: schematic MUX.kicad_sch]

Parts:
IC1, IC2: TMUX1574PWR; Mouser Part Number 595-TMUX1574PWR

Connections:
/GYRO1_INT: IC1.9 (D3); also elsewhere on the board
/GYRO2_INT: IC1.12 (D4); also elsewhere on the board
/I2C_SCL: IC2.4 (D1); also elsewhere on the board
/I2C_SDA: IC2.7 (D2); also elsewhere on the board
/IMU1_INT: IC1.4 (D1); also elsewhere on the board
/IMU2_INT: IC1.7 (D2); also elsewhere on the board
/MUX/MCU_Block/MCU1_GYRO1_INT: IC1.10 (S3B); also elsewhere on the board
/MUX/MCU_Block/MCU1_GYRO2_INT: IC1.13 (S4B); also elsewhere on the board
/MUX/MCU_Block/MCU1_I2C1_SCL_Sens: IC2.2 (S1A); also elsewhere on the board
/MUX/MCU_Block/MCU1_I2C1_SDA_Sens: IC2.5 (S2A); also elsewhere on the board
/MUX/MCU_Block/MCU1_IMU1_INT: IC1.2 (S1A); also elsewhere on the board
/MUX/MCU_Block/MCU1_IMU2_INT: IC1.5 (S2A); also elsewhere on the board
/MUX/MCU_Block/MCU1_SENS_EN: IC2.10 (S3B); also elsewhere on the board
/MUX/MCU_Block/MCU2_GYRO1_INT: IC1.11 (S3A); also elsewhere on the board
/MUX/MCU_Block/MCU2_GYRO2_INT: IC1.14 (S4A); also elsewhere on the board
/MUX/MCU_Block/MCU2_I2C1_SCL_Sens: IC2.3 (S1B); also elsewhere on the board
/MUX/MCU_Block/MCU2_I2C1_SDA_Sens: IC2.6 (S2B); also elsewhere on the board
/MUX/MCU_Block/MCU2_IMU1_INT: IC1.3 (S1B); also elsewhere on the board
/MUX/MCU_Block/MCU2_IMU2_INT: IC1.6 (S2B); also elsewhere on the board
/MUX/MCU_Block/MCU2_SENS_EN: IC2.11 (S3A); also elsewhere on the board
/MUX/MUX_MR: IC1.15 (~EN), IC2.15 (~EN); also elsewhere on the board
/MUX/MUX_SEL: IC1.1 (SEL), IC2.1 (SEL); also elsewhere on the board
/MUX/VCC_MUX: IC1.16 (VDD), IC2.16 (VDD); also elsewhere on the board
/SENS_EN: IC2.9 (D3); also elsewhere on the board
GND: IC1.8 (GND), IC2.8 (GND); also elsewhere on the board
